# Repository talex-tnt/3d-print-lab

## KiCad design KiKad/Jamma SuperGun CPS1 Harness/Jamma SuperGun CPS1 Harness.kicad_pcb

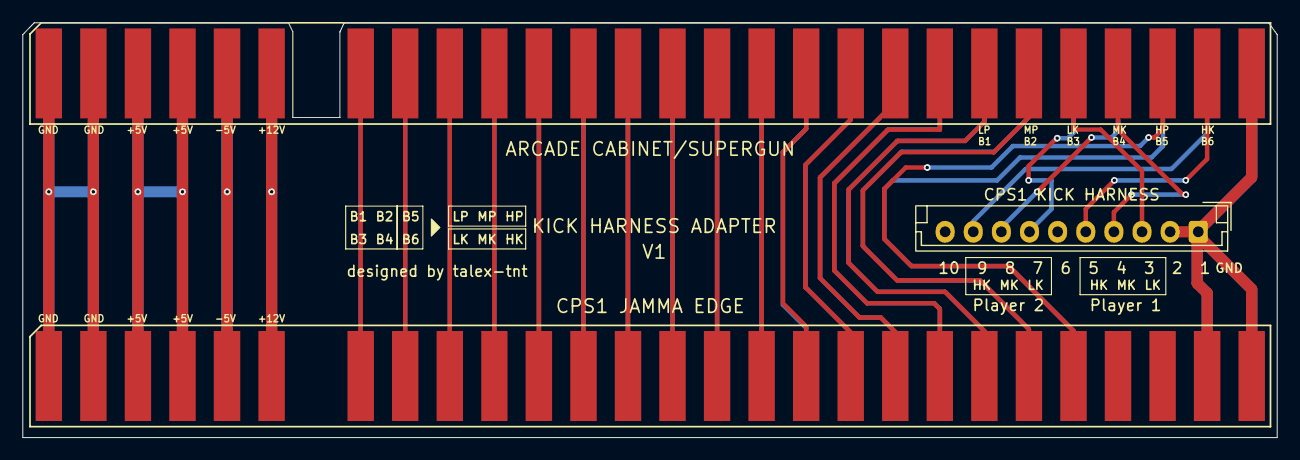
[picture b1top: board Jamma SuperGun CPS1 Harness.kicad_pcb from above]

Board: 2 copper layers, 111.5 x 36.9 mm, 3 parts (0 on the bottom side), 44 nets.

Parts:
ARCADE CABINET/SUPERGUN: JAMMA-56
CPS1 JAMMA EDGE: JAMMA-56
CPS1 KICK HARNESS: JST_EH_B10B-EH-A_1x10_P2.50mm_Vertical

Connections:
/1P Coin: ARCADE CABINET/SUPERGUN.16, CPS1 JAMMA EDGE.16
/1P Down: ARCADE CABINET/SUPERGUN.19, CPS1 JAMMA EDGE.19
/1P Left: ARCADE CABINET/SUPERGUN.20, CPS1 JAMMA EDGE.20
/1P Right: ARCADE CABINET/SUPERGUN.21, CPS1 JAMMA EDGE.21
/1P Start: ARCADE CABINET/SUPERGUN.17, CPS1 JAMMA EDGE.17
/1P Up: ARCADE CABINET/SUPERGUN.18, CPS1 JAMMA EDGE.18
/1P_HK: ARCADE CABINET/SUPERGUN.27, CPS1 KICK HARNESS.5
/1P_HP: ARCADE CABINET/SUPERGUN.26, CPS1 JAMMA EDGE.24
/1P_LK: ARCADE CABINET/SUPERGUN.24, CPS1 KICK HARNESS.3
/1P_LP: ARCADE CABINET/SUPERGUN.22, CPS1 JAMMA EDGE.22
/1P_MK: ARCADE CABINET/SUPERGUN.25, CPS1 KICK HARNESS.4
/1P_MP: ARCADE CABINET/SUPERGUN.23, CPS1 JAMMA EDGE.23
/2P Coin: ARCADE CABINET/SUPERGUN.T, CPS1 JAMMA EDGE.T
/2P Down: ARCADE CABINET/SUPERGUN.W, CPS1 JAMMA EDGE.W
/2P Left: ARCADE CABINET/SUPERGUN.X, CPS1 JAMMA EDGE.X
/2P Right: ARCADE CABINET/SUPERGUN.Y, CPS1 JAMMA EDGE.Y
/2P Start: ARCADE CABINET/SUPERGUN.U, CPS1 JAMMA EDGE.U
/2P Up: ARCADE CABINET/SUPERGUN.V, CPS1 JAMMA EDGE.V
/2P_HK: ARCADE CABINET/SUPERGUN.e, CPS1 KICK HARNESS.9
/2P_HP: ARCADE CABINET/SUPERGUN.d, CPS1 JAMMA EDGE.b
/2P_LK: ARCADE CABINET/SUPERGUN.b, CPS1 KICK HARNESS.7
/2P_LP: ARCADE CABINET/SUPERGUN.Z, CPS1 JAMMA EDGE.Z
/2P_MK: ARCADE CABINET/SUPERGUN.c, CPS1 KICK HARNESS.8
/2P_MP: ARCADE CABINET/SUPERGUN.a, CPS1 JAMMA EDGE.a
/+5V: ARCADE CABINET/SUPERGUN.3, ARCADE CABINET/SUPERGUN.4, ARCADE CABINET/SUPERGUN.C, ARCADE CABINET/SUPERGUN.D, CPS1 JAMMA EDGE.3, CPS1 JAMMA EDGE.4, CPS1 JAMMA EDGE.C, CPS1 JAMMA EDGE.D
/+12V: ARCADE CABINET/SUPERGUN.6, ARCADE CABINET/SUPERGUN.F, CPS1 JAMMA EDGE.6, CPS1 JAMMA EDGE.F
/-5V: ARCADE CABINET/SUPERGUN.5, ARCADE CABINET/SUPERGUN.E, CPS1 JAMMA EDGE.5, CPS1 JAMMA EDGE.E
/Audio GND: ARCADE CABINET/SUPERGUN.M, CPS1 JAMMA EDGE.M
/Audio+: ARCADE CABINET/SUPERGUN.11, CPS1 JAMMA EDGE.11
/Coin Counter 1: ARCADE CABINET/SUPERGUN.8, CPS1 JAMMA EDGE.8
/Coin Counter 2: ARCADE CABINET/SUPERGUN.J, CPS1 JAMMA EDGE.J
/GND: ARCADE CABINET/SUPERGUN.1, ARCADE CABINET/SUPERGUN.2, ARCADE CABINET/SUPERGUN.28, ARCADE CABINET/SUPERGUN.A, ARCADE CABINET/SUPERGUN.B, ARCADE CABINET/SUPERGUN.f, CPS1 JAMMA EDGE.1, CPS1 JAMMA EDGE.2, CPS1 JAMMA EDGE.27, CPS1 JAMMA EDGE.28, CPS1 JAMMA EDGE.A, CPS1 JAMMA EDGE.B, CPS1 JAMMA EDGE.e, CPS1 JAMMA EDGE.f, CPS1 KICK HARNESS.1, CPS1 KICK HARNESS.2
/Lockout 1: ARCADE CABINET/SUPERGUN.9, CPS1 JAMMA EDGE.9
/Lockout 2: ARCADE CABINET/SUPERGUN.K, CPS1 JAMMA EDGE.K
/Service Switch: ARCADE CABINET/SUPERGUN.R, CPS1 JAMMA EDGE.R
/Speaker+: ARCADE CABINET/SUPERGUN.10, CPS1 JAMMA EDGE.10
/Speaker-: ARCADE CABINET/SUPERGUN.L, CPS1 JAMMA EDGE.L
/Test Switch: ARCADE CABINET/SUPERGUN.15, CPS1 JAMMA EDGE.15
/Tilt Switch: ARCADE CABINET/SUPERGUN.S, CPS1 JAMMA EDGE.S
/Video Blue: ARCADE CABINET/SUPERGUN.13, CPS1 JAMMA EDGE.13
/Video GND: ARCADE CABINET/SUPERGUN.14, CPS1 JAMMA EDGE.14
/Video Green: ARCADE CABINET/SUPERGUN.N, CPS1 JAMMA EDGE.N
/Video Red: ARCADE CABINET/SUPERGUN.12, CPS1 JAMMA EDGE.12
/Video Sync: ARCADE CABINET/SUPERGUN.P, CPS1 JAMMA EDGE.P

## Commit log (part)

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2026-03-17 some of my models + some others fixed
2026-03-17 large hole
2026-03-24 first draft of the cps1 board
2026-03-24 add some more detail to the cps1 board
2026-03-24 draft
2026-03-24 adjustments
2026-03-26 spreedsheets
2026-03-30 first draft
2026-03-30 new spreadsheets
2026-04-01 great stuff
2026-04-07 minor changes
2026-04-07 vertical disk holder
2026-04-07 further updates
2026-04-07 further changes
2026-04-12 dual shock stabilizer imgs
2026-04-14 lots of good stuff
2026-04-14 improvements
2026-04-15 fixes
2026-04-17 prints
2026-05-06 multiscart model
2026-05-06 bottom case left
2026-05-06 bottom case left refinements
2026-05-06 bottom case right and refinements
2026-05-06 top left case
2026-05-06 top right case
2026-05-07 front panel
2026-05-07 small adjustments
2026-05-08 add vertical stand
2026-05-11 fix: scart hole size
